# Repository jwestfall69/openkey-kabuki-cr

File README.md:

# openkey-kabuki-cr

  * [Overview](#overview)
  * [Project Status](#project-status)
  * [Support Games](#support-games)
      - [Mitchell](#mitchell)
      - [CPS 1.5 (QSound CPU)](#cps-15--qsound-cpu-)
  * [Hardware](#hardware)
      - [PCB Manufacturing](#pcb-manufacturing)
      - [BOM](#bom)
      - [Assembly](#assembly)
  * [Programming](#programming)
      - [Hardware](#hardware-1)
      - [Software](#software)
  * [Dead Battery Society Removal](#dead-battery-society-removal)
      - [Mitchell DBS Identify/Removal](#mitchell-dbs-identify-removal)
      - [CPS 1.5 (QSound CPU) DBS Identify/Removal](#cps-15--qsound-cpu--dbs-identify-removal)
  * [Installation](#installation)

## Overview
This is an alternate version of the original [openkey kabubki](https://github.com/jwestfall69/openkey-kabuki).  One thing I never really liked about the original is it felt like it was always at risk of popping out of the cpu socket.  This alternate version goes on the underside of the arcade PCB by soldering to the pins of the CPU socket.

I wasn't sure what to call this version, but decided on 'openkey kabuki CR'. CR standing for cost reduced.  While the lower cost is not why I made this version, the BOM does go from ~$5 down to ~$0.60.  

Installed (cps 1.5 D board):<br>

This project is providing the same functionality as [Undamned's InfiniKey-Kabuki](https://www.arcade-projects.com/threads/infinikey-kabuki.8338/).  The lack of supply is what prompted me to make openkey-kabuki.  If they ever end up coming back in stock please consider purchasing those to support [Undamned](https://www.arcade-projects.com/forums/temple-of-the-undamned.77/)'s work.

Details on *how* to program a kabuki CPU's key data can be found in [Eduardo Cruz](http://arcadehacker.blogspot.com/)'s [write up](http://arcadehacker.blogspot.com/2014/11/capcom-kabuki-cpu-intro.html) and [youtube video](https://www.youtube.com/watch?v=9t-9hQEOjLI).

Details on *what* to program can be found in MAME's decryption code for the [kabuki CPU](https://github.com/mamedev/mame/blob/master/src/mame/capcom/kabuki.cpp#L73).

## Project Status
**PCB:** I would consider the design PCB done at this point.  I'm open to any input on changes/improvements.

**Firmware:** Need to get untested games tested

**Documentation:** Done

## Support Games
Openkey Kabuki CR uses solder jumpers for picking the game key.

Below is a list of supported games and what jumpers must be used for each.  This list/table is the same as the original openkey kabuki.

#### Mitchell
| Jumper<br>12345 | Program ROM Labels | MAME Sets | Game Names | Tested / Working |
|-----------------|:------------------:|-----------|--------------|:-----------------:|
| 00000 | BLE<br>BLJ | block<br>blockj | Block Block | YES (conversion)|
| 00001 | CBJ | cbasebal | Capcom Baseball | |
| 00010 | CW | cworld | Capcom World | YES (conversion) |
| 00011 | D2 | dokaben2 | Dokaben 2 | YES (conversion) |
| 00100 | DB | dokaben | Dokaben | YES (conversion) |
| 00101 | MG2 | mgakuen2 | Mahjong Gakuen 2 Gakuen-chou no Fukushuu | YES |
| 00110 | MG3 | marukin | Super Marukin-Ban | YES (conversion) |
| 00111 | PK<br>PKO | pkladiesl<br>pkladies | Poker Ladies | YES (conversion) |
| 01000 | PWE<br>PWJ<br>PWU | pang<br>pompingw<br>bbros | Pang<br>Pomping World<br>Buster Bros | YES |
| 01001 | Q2 | hatena | Adventure Quiz 2 - Hatena? no Daibouken | YES (conversion) |
| 01010 | Q3 | qtono1 | Quiz Tonosama no Yabou | YES |
| 01011 | Q4 | qsangoku | Quiz Sangokushi | YES |
| 01100 | SPE | spang | Super Pang (World) | YES |
| 01101 | SPJ | spangj | Super Pang (Japan) | YES |
| 01110 | SPU | sbbros | Super Buster Bros | YES |
| 01111 | ??? | ??? | Ashita Tenki ni Naare  (place holder) | |

#### CPS 1.5 (QSound CPU)
| Jumper<br>12345 | Program ROM Labels | MAME Sets | Game Names | Tested / Working |
|-----------------|:------------------:|-----------|--------------|:-----------------:|
| 10000 | CDE<br>CDJ<br>CDT<br>CDU | dino<br>dinoj<br>dinoa<br>dinou | Cadillacs and Dinosaurs | |
| 10001 | MBE<br>MBJ<br>MBU<br>MBDE<br>MBDJ | slammast<br>mbomberj<br>slammastu<br>mbombrd<br>mbombrdj | Saturday Night Slam Masters<br>Muscle Bomber<br>Muscle Bomber Duo | YES |
| 10010 | PSE<br>PSH<br>PSJ<br>PSE | punisher<br>punisherh<br>punisherj<br>punisheru | Punisher | YES |
| 10011 | TK2A<br>TK2E<br>TK2J<br>TK2U | wofa<br>wof<br>wofj<br>wofu | Warriors of Fate | YES |

**IMPORTANT**: There is a compatibility issue with the older 92636D-3 revision of the D board.  Specifics on this issue can be found [here](https://www.arcade-projects.com/threads/openkey-kabuki-project.23571/post-370690)

When openkey-kabuki is used on a 92636D-3 board revision you will get:

  * "RAM ERROR" screen on Warriors of Fate
  * "1111 EXCEPTION" screen on Slam Masters
  * "NG" screen on Muscle Bomber Duo
  * A black screen on Punisher and C&D

Thus far I've only seen WOF using this older version of the D board.

The compatibility issue was tracked down to a bug in the D9K1 PAL thats on 92636D-3.  The fix is to upgrade that PAL to D9K2, which is found on the newer revision of the D board (92636D-5).

## Hardware
---
#### PCB Manufacturing
For board thickness the default of 1.6mm is probably fine, but for my first run of the boards I used 1.0mm.  This is slim enough that the CPU socket pins stick a little bit above the openkey kabuki CR board..

I've been using [jlcpcb](https://jlcpcb.com/) for PCB manufacturing.  

#### BOM
| Description | Part Number | DigiKey | Mouser | Notes |
|-------------|-------------|---------|--------|-------|
| ATtiny404 20Mhz | ATTINY404-SSN | [ATTINY404-SSN-ND](https://www.digikey.com/en/products/detail/microchip-technology/ATTINY404-SSN/9947546) | [556-ATTINY404-SSNR](https://www.mouser.com/ProductDetail/Microchip-Technology-Atmel/ATTINY404-SSNR?qs=F5EMLAvA7IAEqD7Aw0z%252B9Q%3D%3D) | Other ATtiny tinyAVR 0/1/2-series models should be viable as well.  The code compiles to just over 1K in size, so any that have 2k or more of flash should work.  Just note I have only tested with 404s |
| 100nf / 0.1uf SMD Ceramic Capacitor 0805 Size | | | | |

**NOTE**: Additional components maybe needed if you need to revert any previously made desuicide modifications to the arcade PCB.  Check the Dead Battery Society Removal section at the bottom for details.

#### Assembly
Nothing special here, just solder the ATtiny404 and bypass capacitor to the board.  You can also solder the jumpers at this point as they won't interfere with programming like they do on openkey-cps2.

## Programming
**IMPORTANT:** Programming should be done before soldering the openkey to the arcade PCB.

#### Hardware
Programming is done with a UPDI programmer.  I've been using this one:

[Serial UPDI Programmer for ATmega 0-Series, or ATtiny 0-Series or 1-Series, or AVR DA or AVR DB](https://www.amazon.com/dp/B09X64YRLD?psc=1&ref=ppx_yo2ov_dt_b_product_details)

Note: This programmer (and likely others) has a switch for 3.3V and 5V.  Set it to 5V.

The openkey kabuki CR programming port consists of 3x pads (VCC, GND, UPDI) that will need to be connected to the programmer.  I've been using a short 3 pin female to female IDC cable with [pogo pins](https://www.amazon.com/dp/B00X7C8PGE?psc=1&ref=ppx_yo2ov_dt_b_product_details) on one end to do this.  Additionally you could probably use something like [this](https://www.amazon.com/dp/B09MGG4C6X?ref=ppx_yo2ov_dt_b_product_details&th=1) if you are going to be programming a bunch.

Of course be sure you properly orient the board so the labeled pads match up.  vcc to vcc, gnd to gnd, and updi to updi.

#### Software
For software I've been using the [Arduino IDE](https://www.arduino.cc/en/software/OldSoftwareReleases) with [megaTinyCore](https://github.com/SpenceKonde/megaTinyCore), which adds support for tinyAVR 0/1/2-Series MCUs.

**NOTE**: The makers of megaTinyCore currently recommend using Arduino IDE version 1.8.13 for best compatibility.  2.0 definitely does not work!

To install the megaTinyCore you, should just need to add http://drazzy.com/package_drazzy.com_index.json to "Additional Boards Manager URLs" in the settings for the Arduino IDE.

From there you need to configure the board/programming settings.  I've been using these:

**IMPORTANT:** The firmware between the original openkey kabuki and the CR version is different, make sure you are using the CR version.

## Dead Battery Society Removal
Prior to installing openkey kabuki CR you should verify you don't have the [The Dead Battery Society](http://www.arcadecollecting.com/dead/) mod installed on your mitchell or cps 1.5 D board.  Part of the DBS mod is to tie pin 28 of the kabuki CPU to GND.  This pin is normally fed voltage from the battery/vcc to supply the CPU with power for its internal ram holding the key data.  openkey-kabuki will not function unless this is reverted.

Below is how you can identify if the DBS mod is been installed and how to remove it.

#### Mitchell DBS Identify/Removal
This is what a dead battery society mod will look like

 * R33 (1k ohm resistor) is missing
 * Right through hole of R33 is bridged to the lower right
 * Those pins on the program roms are soldered together and have a wire from them to a pin on the cpu
 * Modified program roms

 All of these things will need to be reverted in order to use openkey-kabuki.  This is what an unmodified board should look like.

#### CPS 1.5 (QSound CPU) DBS Identify/Removal

This is what the dead battery society mod will look like on the QSound board of a cps 1.5 game.

Top Side:<br>

* R33 (1 ohm resistor 0805 size) is missing
* C12 (100nf capacitor 0805 size) is replaced with a jumper
* Modified QSound program rom

Bottom Side:<br>

* Wire running from QSound program rom pin 30 to Kabuki CPU pin 27
* Cut trace between QSound program rom pins 30 and 31

There will be additional changes specific to slam masters / muscle bomber which are not covered above.

Once reverted it should look like this

Top Side:<br>

Bottom Side:<br>

Its hard to tell from the picture, but pins 30 and 31 on the QSound program rom are jumper'd together.

## Installation
openkey kabuki CR gets soldered to the underside of the kabuki CPU socket.  There are a couple things to do before soldering.

* Straighten any CPU socket pins that are bent
* Clean any oxidation or corrosion off the CPU socket pins

The openkey kabuki CR board should be oriented so the notch in the silk screen (near #5 in the key select) is facing the same direction as the notch on the CPU/socket on the top side of the arcade PCB.  In theory it should be towards the jamma edge as well.

Only a handful of pins need to be soldered for openkey kabuki CR to be functional, as seen below.

Its advised you initially only solder these pins, then test.  If there ends up being an issue, it will be a lot less work to desolder 8 pins then 40.

Once it tests ok, go ahead and solder the rest of the pins.

Below are example installations

Pang/Super Pang Style Boards:<br>

CPS 1.5 D Board:<br>

Block Block / Poker Ladies / Quiz Style Boards:<br>

Mahjong Style Boards:<br>

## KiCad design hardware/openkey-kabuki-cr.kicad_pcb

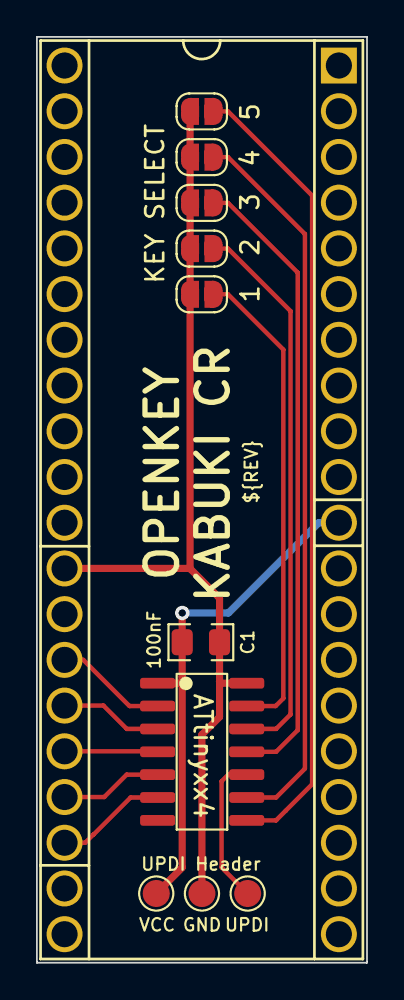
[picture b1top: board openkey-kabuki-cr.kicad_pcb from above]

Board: 2 copper layers, 18.3 x 51.4 mm, 11 parts (1 on the bottom side), 13 nets.

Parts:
C1: 100nF; C_0805_2012Metric_Pad1.18x1.45mm_HandSolder
J2: VCC; TestPoint_Pad_D1.5mm
J3: GND; TestPoint_Pad_D1.5mm
J4: J5 / UDPI; TestPoint_Pad_D1.5mm
JP1, JP2, JP3, JP4, JP5: SolderJumper_2_Open; SolderJumper-2_P1.3mm_Open_RoundedPad1.0x1.5mm
U1: ATtinyxx4; SOIC-14_3.9x8.7mm_P1.27mm
U2: KABUKICPU; DIP-40_W15.24mm_Socket_Wide_Holes

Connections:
/BUSACK: U1.6 (PB3), U2.23 (~BUSACK)
/BUSREQ: U1.4 (PA6), U2.25 (~BUSRQ)
/M1: U1.2 (PA4), U2.27 (~M1)
/RESET: U1.3 (PA5), U2.26 (~RESET)
/SW1-1: JP1.1 (A), U1.13 (PA3)
/SW1-2: JP2.1 (A), U1.12 (PA2)
/SW1-3: JP3.1 (A), U1.11 (PA1)
/SW1-4: JP4.1 (A), U1.9 (PB0)
/SW1-5: JP5.1 (A), U1.8 (PB1)
/UPDI: J4.1, U1.10 (~RESET/PA0)
/WAIT: U1.5 (PA7), U2.24 (~WAIT)
GND: C1.2, J3.1, JP1.2 (B), JP2.2 (B), JP3.2 (B), JP4.2 (B), JP5.2 (B), U1.14 (GND), U2.29 (GND)
VCC: C1.1, J2.1, U1.1 (VCC), U2.11 (VCC)

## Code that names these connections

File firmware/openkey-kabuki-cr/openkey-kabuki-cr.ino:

// openkey-kabuki-cr firmware
#include <avr/sleep.h>

// PIN 6 (PIN_B3) <=> Kabuki PIN 23 (BUSACK)
#define SET_BUSACK    PORTB.OUTSET = PIN3_bm
#define CLR_BUSACK    PORTB.OUTCLR = PIN3_bm

// PIN 5 (PIN_A7) <=> Kabuki PIN 24 (WAIT)
#define SET_WAIT      PORTA.OUTSET = PIN7_bm
#define CLR_WAIT      PORTA.OUTCLR = PIN7_bm

// PIN 4 (PIN_A6) <=> Kabuki PIN 25 (BUSREQ)
#define SET_BUSREQ    PORTA.OUTSET = PIN6_bm
#define CLR_BUSREQ    PORTA.OUTCLR = PIN6_bm

// PIN 3 (PIN_A5) <=> Kabuki PIN 26 (RESET)
#define SET_RESET     PORTA.OUTSET = PIN5_bm
#define CLR_RESET     PORTA.OUTCLR = PIN5_bm

// PIN 2 (PIN_A4) <=> Kabuki PIN 27 (M1)
#define SET_M1        PORTA.OUTSET = PIN4_bm
#define CLR_M1        PORTA.OUTCLR = PIN4_bm

// First 4 fields come from mame @
// https://github.com/mamedev/mame/blob/master/src/mame/capcom/kabuki.cpp#L73
// mem_mask field comes from Eduardo Cruz (ArcadeHacker). 
// https://github.com/ArcadeHacker/ArcadeHacker_Kabuki/blob/master/ArcadeHacker_Kabuki.ino#L33
typedef struct game_key_t {
  uint32_t swap_key1;
  uint32_t swap_key2;
  uint16_t address_key;
   uint8_t xor_key;
  uint16_t mem_mask;
} game_key;

#define MAX_GAME_NUM   20
game_key game_keys[MAX_GAME_NUM + 1] = {
  // mitchell games                                      dsw
  //   skey1       skey2     addr    xor   mask         12345
  { 0x02461357, 0x64207531, 0x0002, 0x01, 0x7000 },  // 00000 [BLx] Block Block (BLE, BLJ)
  { 0x01234567, 0x76543210, 0x6548, 0x24, 0x7000 },  // 00001 [CBJ] Capcom Baseball
  { 0x04152637, 0x40516273, 0x5751, 0x43, 0x7000 },  // 00010 [CW]  Capcom World
  { 0x76543210, 0x01234567, 0xaa55, 0xa5, 0x7000 },  // 00011 [D2]  Dokaben 2
  { 0x76543210, 0x01234567, 0xaa55, 0xa5, 0x7000 },  // 00100 [DB]  Dokaben
  { 0x76543210, 0x01234567, 0xaa55, 0xa5, 0x7000 },  // 00101 [MG2] Mahjong Gakuen 2 Gakuen-chou no Fukushuu
  { 0x54321076, 0x54321076, 0x4854, 0x4f, 0x7000 },  // 00110 [MG3] Super Marukin-Ban
  { 0x76543210, 0x01234567, 0xaa55, 0xa5, 0x7000 },  // 00111 [PKx] Poker Ladies (PK, PKO)
  { 0x01234567, 0x76543210, 0x6548, 0x24, 0xf000 },  // 01000 [PWx] Pang / Buster Bros / Pomping World (PWE, PWJ, PWU)
  { 0x45670123, 0x45670123, 0x5751, 0x43, 0x7000 },  // 01001 [Q2]  Adventure Quiz 2 Hatena ? no Dai-Bouken
  { 0x12345670, 0x12345670, 0x1111, 0x11, 0x7000 },  // 01010 [Q3]  Quiz Tonosama no Yabou
  { 0x23456701, 0x23456701, 0x1828, 0x18, 0x7000 },  // 01011 [Q4]  Quiz Sangokushi
  { 0x45670123, 0x45670123, 0x5852, 0x43, 0x7000 },  // 01100 [SPE] Super Pang World
  { 0x45123670, 0x67012345, 0x55aa, 0x5a, 0x7000 },  // 01101 [SPJ] Super Pang Japan
  { 0x45670123, 0x45670123, 0x2130, 0x12, 0x7000 },  // 01110 [SPU] Super Buster Bros
  { 0x00000000, 0x00000000, 0x0000, 0x00, 0x0000 },  // 01111 [???] Ashita Tenki ni Naare (unknown)

  // cps1.5 games                                        dsw
  //   skey1       skey2     addr    xor   mask         12345
  { 0x76543210, 0x24601357, 0x4343, 0x43, 0xff00 },  // 10000 [CDx] Cadillacs and Dinosaurs (CDE, CDJ, CDT, CDU)
  { 0x54321076, 0x65432107, 0x3131, 0x19, 0xff00 },  // 10001 [MBx] Slam Masters (MBDE, MBDJ, MBE, MBJ, MBU)
  { 0x67452103, 0x75316024, 0x2222, 0x22, 0xff00 },  // 10010 [PSx] Punisher (PS, PSE, PSH, PSU)
  { 0x01234567, 0x54163072, 0x5151, 0x51, 0xff00 },  // 10011 [TKx] Warrior of Fate (TK2A, TK2E, TK2J, TK2U)

  // bad dsw value / zero key
  { 0x00000000, 0x00000000, 0x0000, 0x00, 0x0000 }
};

// doing bit shifting takes a variable amount
// of time depending on the how far the shift
// is.  Using the below lookup table to keep
// a consistent clock period when masking a
// bit to send. 
uint32_t masks[32] = {
  0x00000001, 0x00000002, 0x00000004, 0x00000008,
  0x00000010, 0x00000020, 0x00000040, 0x00000080,
  0x00000100, 0x00000200, 0x00000400, 0x00000800,
  0x00001000, 0x00002000, 0x00004000, 0x00008000,
  0x00010000, 0x00020000, 0x00040000, 0x00080000,
  0x00100000, 0x00200000, 0x00400000, 0x00800000,
  0x01000000, 0x02000000, 0x04000000, 0x08000000,
  0x10000000, 0x20000000, 0x40000000, 0x80000000,
};

void setup() {
  
  // wait a bit for other IC's on the board to get
  // in their inital states
  delay(100);

  // wait for the WAIT pin on the kabuki to go high
  // before we do anything
  while(!PORTA.IN & PIN7_bm) { }
  
  // set the pins to kabuki as outputs
  PORTA.DIR = PIN4_bm | PIN5_bm | PIN6_bm | PIN7_bm;
  PORTB.DIR = PIN3_bm;

  // stage #1: set initial output states
  // https://www.youtube.com/watch?v=9t-9hQEOjLI&t=754s
  CLR_RESET;
  CLR_WAIT;
  CLR_BUSREQ;
  SET_M1;
  SET_BUSACK;

  // enable pull-ups on dsw pins
  PORTA.PIN3CTRL |= PORT_PULLUPEN_bm;  // PIN 13 (PIN_PA3) <=> DSW5
  PORTA.PIN2CTRL |= PORT_PULLUPEN_bm;  // PIN 12 (PIN_PA2) <=> DSW4
  PORTA.PIN1CTRL |= PORT_PULLUPEN_bm;  // PIN 11 (PIN_PA1) <=> DSW3
  PORTB.PIN0CTRL |= PORT_PULLUPEN_bm;  // PIN  9 (PIN_PB0) <=> DSW2
  PORTB.PIN1CTRL |= PORT_PULLUPEN_bm;  // PIN  8 (PIN_PB1) <=> DSW1

  // stage #2: door knock #1
  // https://www.youtube.com/watch?v=9t-9hQEOjLI&t=871s
  for(int i = 0;i < 3;i++) {
    SET_BUSREQ;
    CLR_BUSREQ;
  }

  // stage #3: unlock key
  // https://www.youtube.com/watch?v=9t-9hQEOjLI&t=1274s
  send_data(0xb7a45, 20, -1);

  // stage #4: door knock #2
  // https://www.youtube.com/watch?v=9t-9hQEOjLI&t=1433s
  for(int i = 0;i < 10;i++) {
    CLR_M1;
    SET_M1;
  }

  uint8_t game_num = read_dsw();
  if(game_num > MAX_GAME_NUM) {
    game_num = MAX_GAME_NUM;
  }

  // stage #5: 108-bit programming
  // https://www.youtube.com/watch?v=9t-9hQEOjLI&t=1518s
  send_data(0x0, 20, -1);
  send_data(game_keys[game_num].address_key, 16, -1);

  // mame swap keys are 32bit, but the actual swap key is 24bit.
  // the conversion process is to drop the top bit from each nibble.
  // below we are looping over each nibble and only sending the
  // lower 3 bits.
  for(int start_bit = 30; start_bit > 0; start_bit -= 4) {
    send_data(game_keys[game_num].swap_key2, 3, start_bit);
  }

  for(int start_bit = 30; start_bit > 0; start_bit -= 4) {
    send_data(game_keys[game_num].swap_key1, 3, start_bit);
  }

  send_data(game_keys[game_num].xor_key, 8, -1);
  send_data(game_keys[game_num].mem_mask, 16, -1);

  // set all pins to be inputs
  PORTA.DIR = 0;
  PORTB.DIR = 0;

  // power down
  set_sleep_mode(SLEEP_MODE_PWR_DOWN);
  sleep_enable();
  sleep_cpu();
}

void loop() {
  while(1) {}
}

// send bits of data starting at start_bit and going MSB to LSB.
// if start_bit is -1, send the last LSB num_bits bits of the data
void send_data(uint32_t data, int8_t num_bits, int8_t start_bit) {
  num_bits--;

  if(start_bit == -1) {
    start_bit = num_bits;
  }

  while(num_bits >= 0) {
    uint32_t bit = data & masks[start_bit];
    if(bit) {
      SET_M1;
    } else {
      CLR_M1;
    }
    CLR_BUSACK;
    SET_BUSACK;
    num_bits--;
    start_bit--;
  }
}

// DSW1 = PA3 = bit4
// DSW2 = PA2 = bit3
// DSW3 = PA1 = bit2
// DSW4 = PB0 = bit1
// DSW5 = PB1 = bit0
uint8_t read_dsw() {
  uint8_t dsw = 0;

  // negate the bits since we are using
  // pull-ups, "on"s will be low
  uint8_t porta = PORTA.IN ^ 0xff;
  uint8_t portb = PORTB.IN ^ 0xff;

  porta = porta & 0xe;
  dsw = porta << 1;

  dsw = dsw | ((portb & 0b00000001) << 1);  // PB0 to bit1
  dsw = dsw | ((portb & 0b00000010) >> 1);  // PB1 to bit0
  return dsw;
}

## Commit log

2024-06-29 Fix up submodule
2024-06-29 Add better pictures
